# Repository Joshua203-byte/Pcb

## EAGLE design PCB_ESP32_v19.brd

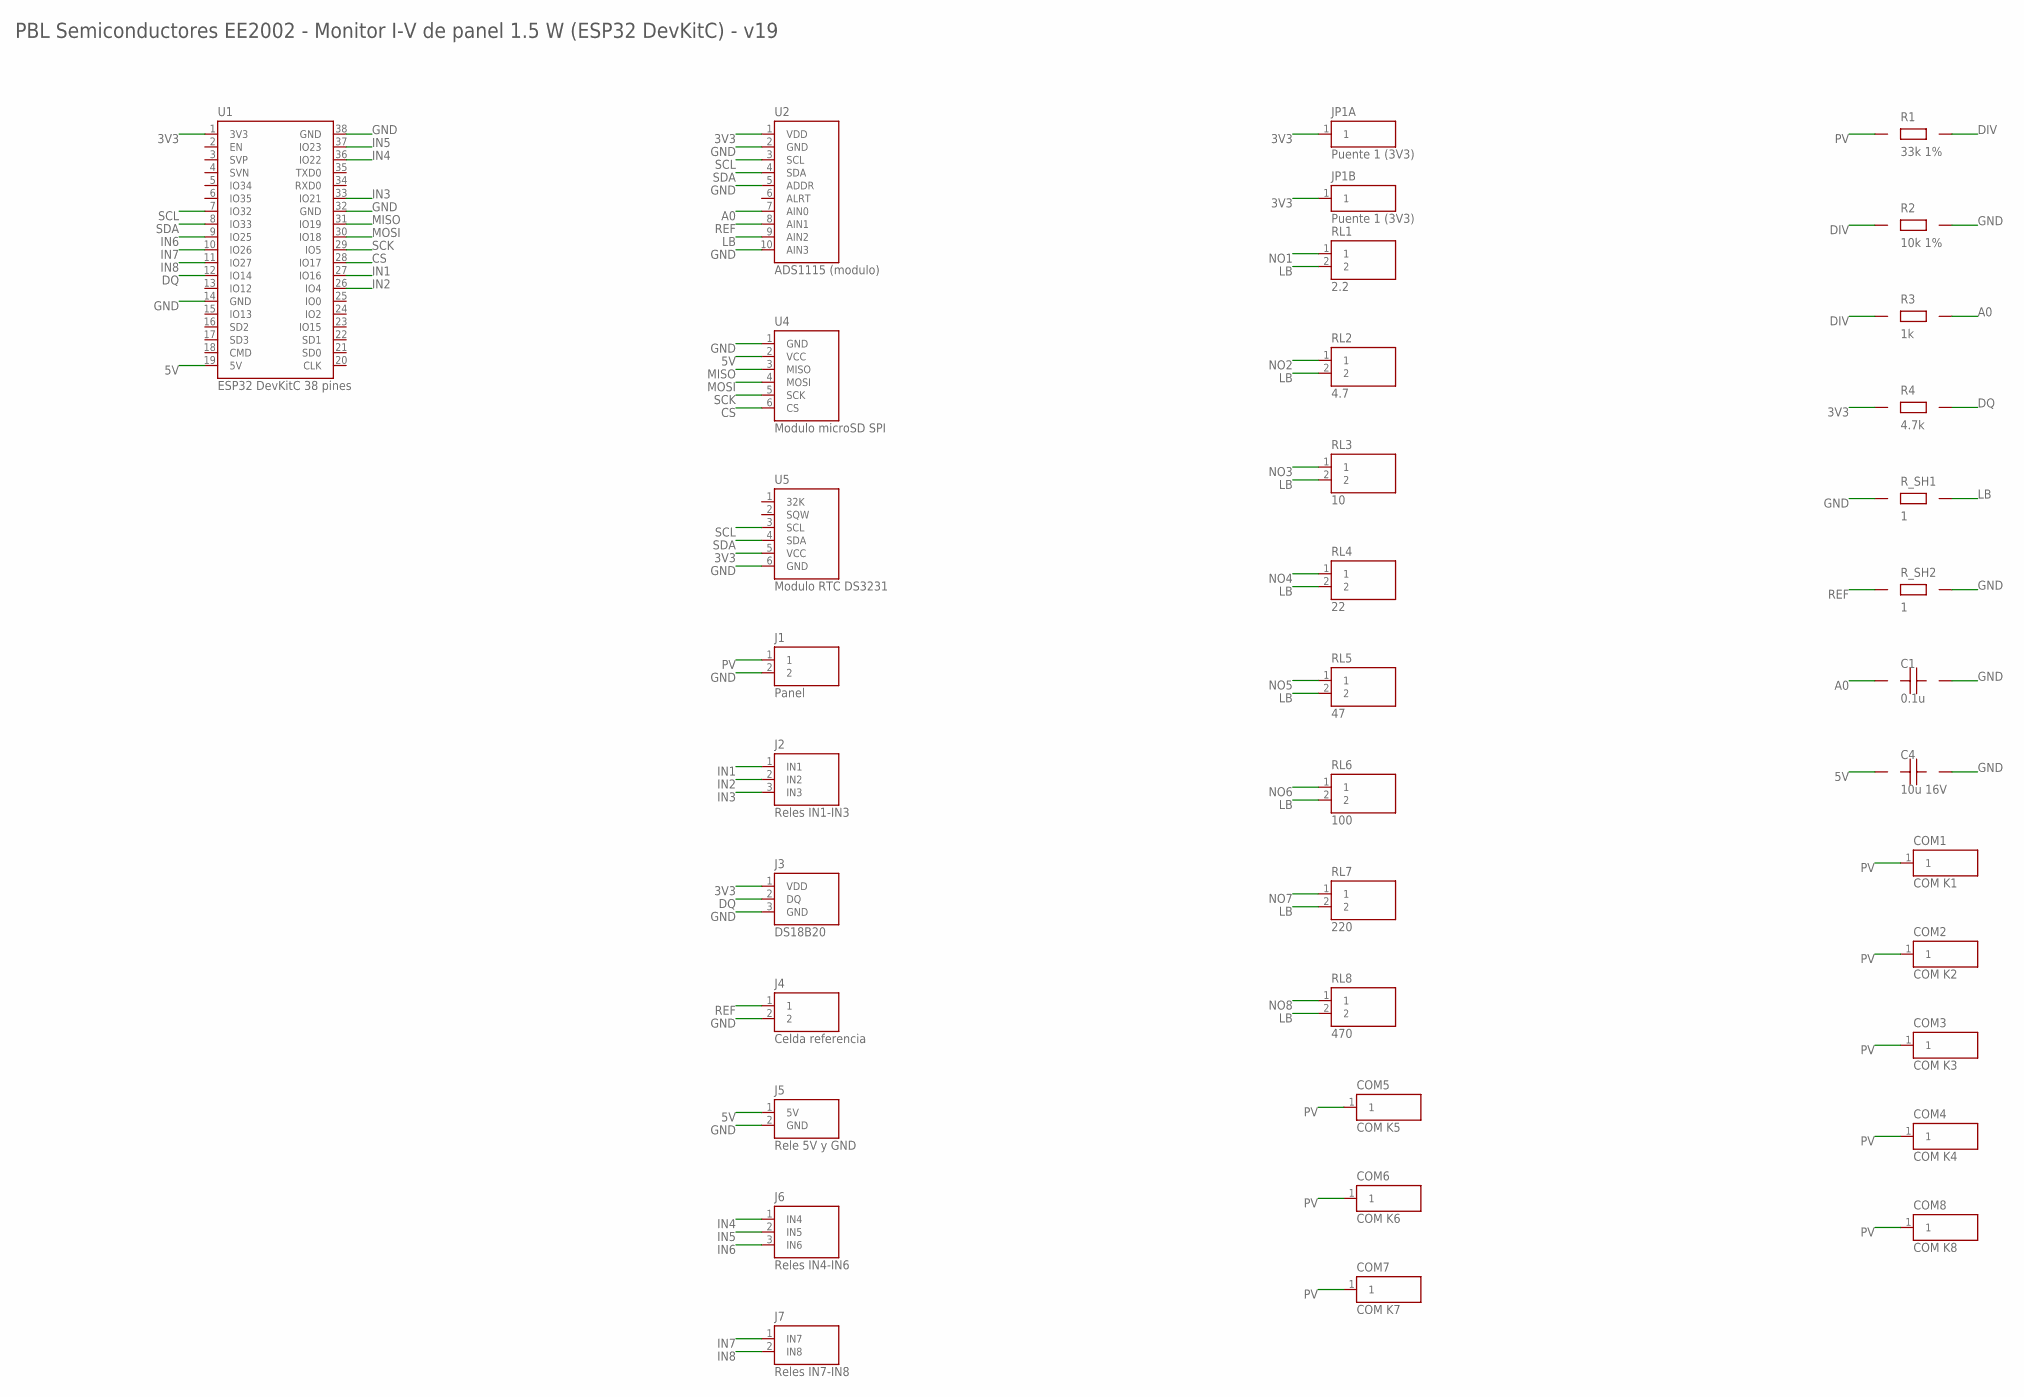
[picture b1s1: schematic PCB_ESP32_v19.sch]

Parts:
C1: 0.1u; CAP_5MM
C4: 10u 16V; CAP_E_2_54
COM1: COM K1; WIREPAD
COM2: COM K2; WIREPAD
COM3: COM K3; WIREPAD
COM4: COM K4; WIREPAD
COM5: COM K5; WIREPAD
COM6: COM K6; WIREPAD
COM7: COM K7; WIREPAD
COM8: COM K8; WIREPAD
J1: Panel; TERM2_5MM
J2: Reles IN1-IN3; MALE_1X03
J3: DS18B20; MALE_1X03
J4: Celda referencia; TERM2_5MM
J5: Rele 5V y GND; MALE_1X02
J6: Reles IN4-IN6; MALE_1X03
J7: Reles IN7-IN8; MALE_1X02
JP1A, JP1B: Puente 1 (3V3); JPAD
R1: 33k 1%; RES_V
R2: 10k 1%; RES_V
R3: 1k; RES_V
R4: 4.7k; RES_V
RL1: 2.2; RES_H_T
RL2: 4.7; RES_H_T
RL3: 10; RES_H_T
RL4: 22; RES_H_T
RL5: 47; RES_H_T
RL6: 100; RES_H_T
RL7: 220; RES_H_T
RL8: 470; RES_H_T
R_SH1, R_SH2: 1; RES_V
U1: ESP32 DevKitC 38 pines; ESP32_DEVKIT38
U2: ADS1115 (modulo); SOCKET_1X10
U4: Modulo microSD SPI; SOCKET_1X06
U5: Modulo RTC DS3231; SOCKET_1X06

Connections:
3V3: J3.1 (VDD), JP1A.1, JP1B.1, R4.1, U1.1 (3V3), U2.1 (VDD), U5.5 (VCC)
5V: C4.1 (+), J5.1 (5V), U1.19 (5V), U4.2 (VCC)
A0: C1.1, R3.2, U2.7 (AIN0)
CS: U1.28 (IO17), U4.6 (CS)
DIV: R1.2, R2.1, R3.1
DQ: J3.2 (DQ), R4.2, U1.12 (IO14)
GND: C1.2, C4.2 (-), J1.2, J3.3 (GND), J4.2, J5.2 (GND), R2.2, R_SH1.1, R_SH2.2, U1.14 (GND), U1.32 (GND), U1.38 (GND), U2.2 (GND), U2.5 (ADDR), U2.10 (AIN3), U4.1 (GND), U5.6 (GND)
IN1: J2.1 (IN1), U1.27 (IO16)
IN2: J2.2 (IN2), U1.26 (IO4)
IN3: J2.3 (IN3), U1.33 (IO21)
IN4: J6.1 (IN4), U1.36 (IO22)
IN5: J6.2 (IN5), U1.37 (IO23)
IN6: J6.3 (IN6), U1.9 (IO25)
IN7: J7.1 (IN7), U1.10 (IO26)
IN8: J7.2 (IN8), U1.11 (IO27)
LB: RL1.2, RL2.2, RL3.2, RL4.2, RL5.2, RL6.2, RL7.2, RL8.2, R_SH1.2, U2.9 (AIN2)
MISO: U1.31 (IO19), U4.3 (MISO)
MOSI: U1.30 (IO18), U4.4 (MOSI)
NO1: RL1.1
NO2: RL2.1
NO3: RL3.1
NO4: RL4.1
NO5: RL5.1
NO6: RL6.1
NO7: RL7.1
NO8: RL8.1
PV: COM1.1, COM2.1, COM3.1, COM4.1, COM5.1, COM6.1, COM7.1, COM8.1, J1.1, R1.1
REF: J4.1, R_SH2.1, U2.8 (AIN1)
SCK: U1.29 (IO5), U4.5 (SCK)
SCL: U1.7 (IO32), U2.3 (SCL), U5.3 (SCL)
SDA: U1.8 (IO33), U2.4 (SDA), U5.4 (SDA)

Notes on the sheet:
PBL Semiconductores EE2002 - Monitor I-V de panel 1.5 W (ESP32 DevKitC) - v19

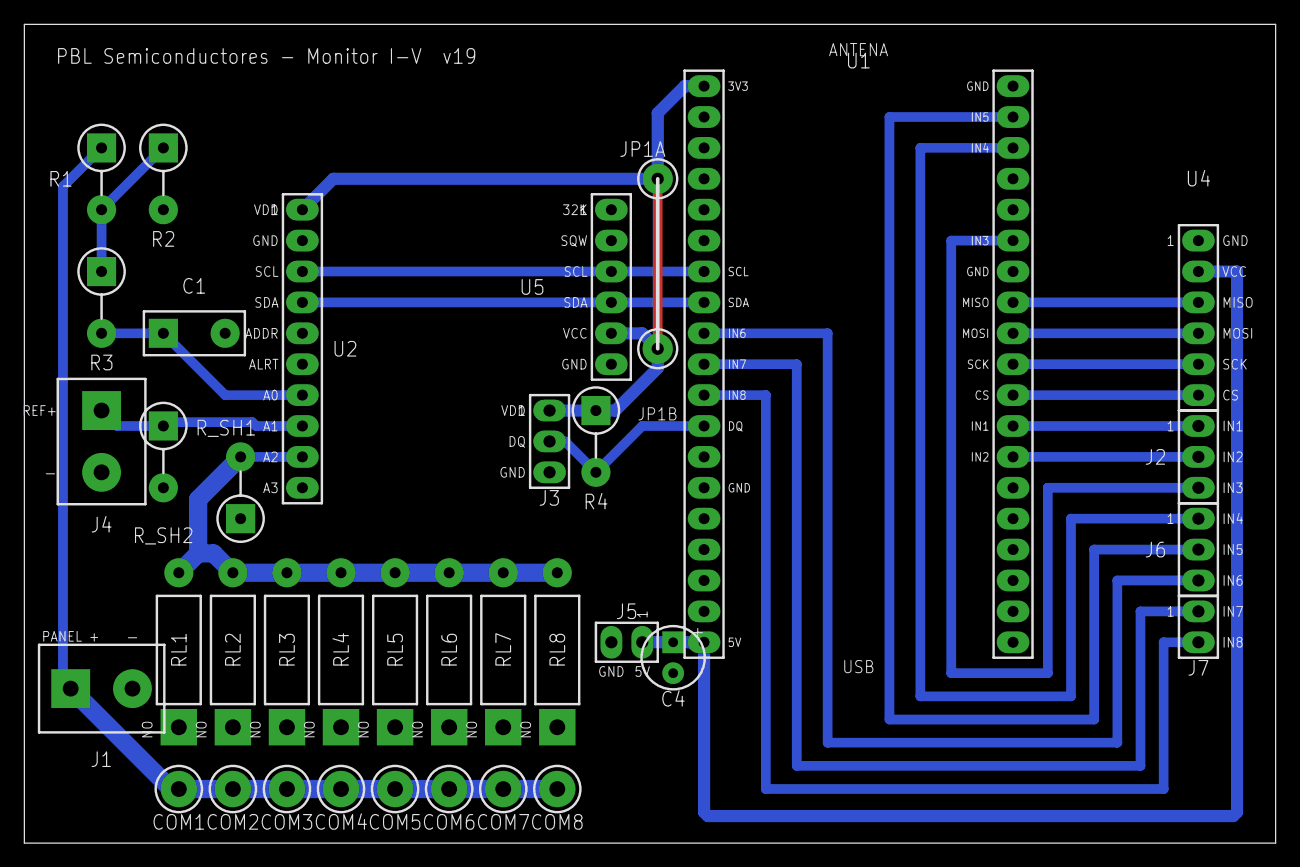
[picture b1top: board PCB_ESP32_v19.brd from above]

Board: 2 copper layers, 102.9 x 67.3 mm, 37 parts (0 on the bottom side), 23 nets.

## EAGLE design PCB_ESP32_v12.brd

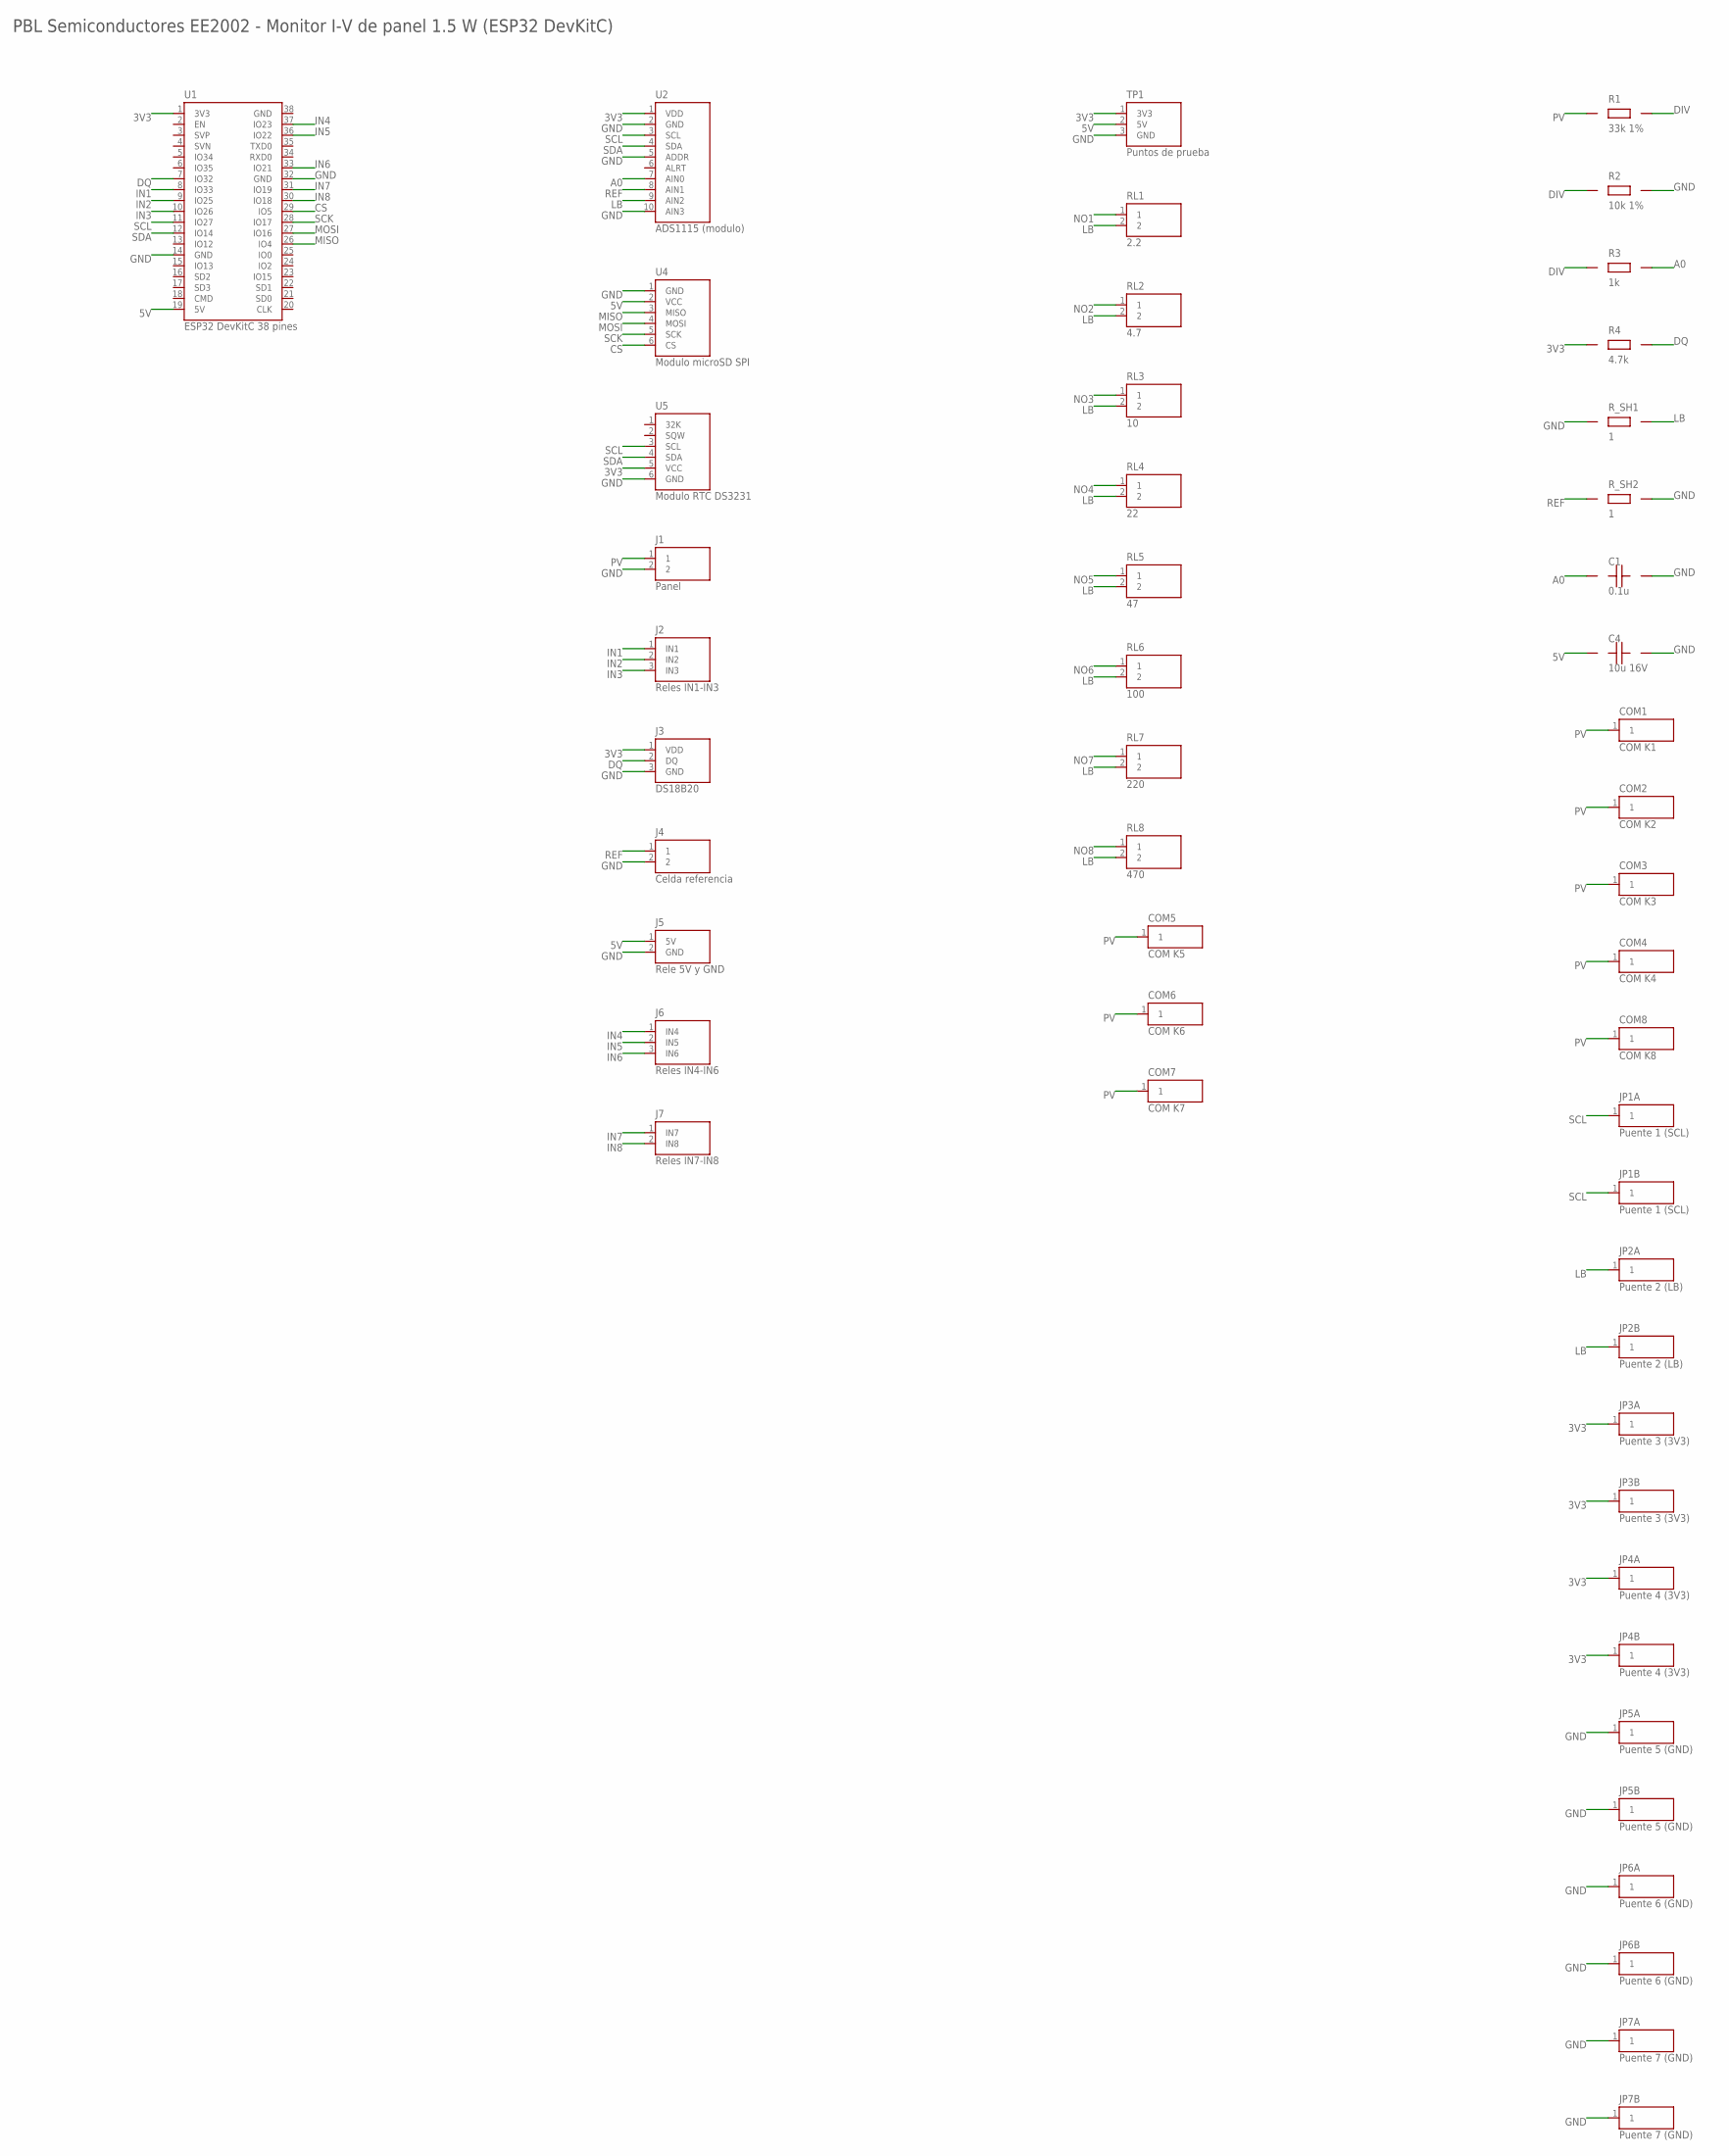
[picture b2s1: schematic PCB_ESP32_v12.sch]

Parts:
C1: 0.1u; CAP_5MM
C4: 10u 16V; CAP_E_2_54
COM1: COM K1; WIREPAD
COM2: COM K2; WIREPAD
COM3: COM K3; WIREPAD
COM4: COM K4; WIREPAD
COM5: COM K5; WIREPAD
COM6: COM K6; WIREPAD
COM7: COM K7; WIREPAD
COM8: COM K8; WIREPAD
J1: Panel; TERM2_5MM
J2: Reles IN1-IN3; MALE_1X03
J3: DS18B20; MALE_1X03
J4: Celda referencia; TERM2_5MM
J5: Rele 5V y GND; MALE_1X02
J6: Reles IN4-IN6; MALE_1X03
J7: Reles IN7-IN8; MALE_1X02
JP1A, JP1B: Puente 1 (SCL); JPAD
JP2A, JP2B: Puente 2 (LB); JPAD
JP3A, JP3B: Puente 3 (3V3); JPAD
JP4A, JP4B: Puente 4 (3V3); JPAD
JP5A, JP5B: Puente 5 (GND); JPAD
JP6A, JP6B: Puente 6 (GND); JPAD
JP7A, JP7B: Puente 7 (GND); JPAD
R1: 33k 1%; RES_V
R2: 10k 1%; RES_V
R3: 1k; RES_V
R4: 4.7k; RES_V
RL1: 2.2; RES_H_T
RL2: 4.7; RES_H_T
RL3: 10; RES_H_T
RL4: 22; RES_H_T
RL5: 47; RES_H_T
RL6: 100; RES_H_T
RL7: 220; RES_H_T
RL8: 470; RES_H_T
R_SH1, R_SH2: 1; RES_V
TP1: Puntos de prueba; MALE_1X03
U1: ESP32 DevKitC 38 pines; ESP32_DEVKIT38
U2: ADS1115 (modulo); SOCKET_1X10
U4: Modulo microSD SPI; SOCKET_1X06
U5: Modulo RTC DS3231; SOCKET_1X06

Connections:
3V3: J3.1 (VDD), JP3A.1, JP3B.1, JP4A.1, JP4B.1, R4.1, TP1.1 (3V3), U1.1 (3V3), U2.1 (VDD), U5.5 (VCC)
5V: C4.1 (+), J5.1 (5V), TP1.2 (5V), U1.19 (5V), U4.2 (VCC)
A0: C1.1, R3.2, U2.7 (AIN0)
CS: U1.29 (IO5), U4.6 (CS)
DIV: R1.2, R2.1, R3.1
DQ: J3.2 (DQ), R4.2, U1.7 (IO32)
GND: C1.2, C4.2 (-), J1.2, J3.3 (GND), J4.2, J5.2 (GND), JP5A.1, JP5B.1, JP6A.1, JP6B.1, JP7A.1, JP7B.1, R2.2, R_SH1.1, R_SH2.2, TP1.3 (GND), U1.14 (GND), U1.32 (GND), U2.2 (GND), U2.5 (ADDR), U2.10 (AIN3), U4.1 (GND), U5.6 (GND)
IN1: J2.1 (IN1), U1.8 (IO33)
IN2: J2.2 (IN2), U1.9 (IO25)
IN3: J2.3 (IN3), U1.10 (IO26)
IN4: J6.1 (IN4), U1.37 (IO23)
IN5: J6.2 (IN5), U1.36 (IO22)
IN6: J6.3 (IN6), U1.33 (IO21)
IN7: J7.1 (IN7), U1.31 (IO19)
IN8: J7.2 (IN8), U1.30 (IO18)
LB: JP2A.1, JP2B.1, RL1.2, RL2.2, RL3.2, RL4.2, RL5.2, RL6.2, RL7.2, RL8.2, R_SH1.2, U2.9 (AIN2)
MISO: U1.26 (IO4), U4.3 (MISO)
MOSI: U1.27 (IO16), U4.4 (MOSI)
NO1: RL1.1
NO2: RL2.1
NO3: RL3.1
NO4: RL4.1
NO5: RL5.1
NO6: RL6.1
NO7: RL7.1
NO8: RL8.1
PV: COM1.1, COM2.1, COM3.1, COM4.1, COM5.1, COM6.1, COM7.1, COM8.1, J1.1, R1.1
REF: J4.1, R_SH2.1, U2.8 (AIN1)
SCK: U1.28 (IO17), U4.5 (SCK)
SCL: JP1A.1, JP1B.1, U1.11 (IO27), U2.3 (SCL), U5.3 (SCL)
SDA: U1.12 (IO14), U2.4 (SDA), U5.4 (SDA)

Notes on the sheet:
PBL Semiconductores EE2002 - Monitor I-V de panel 1.5 W (ESP32 DevKitC)

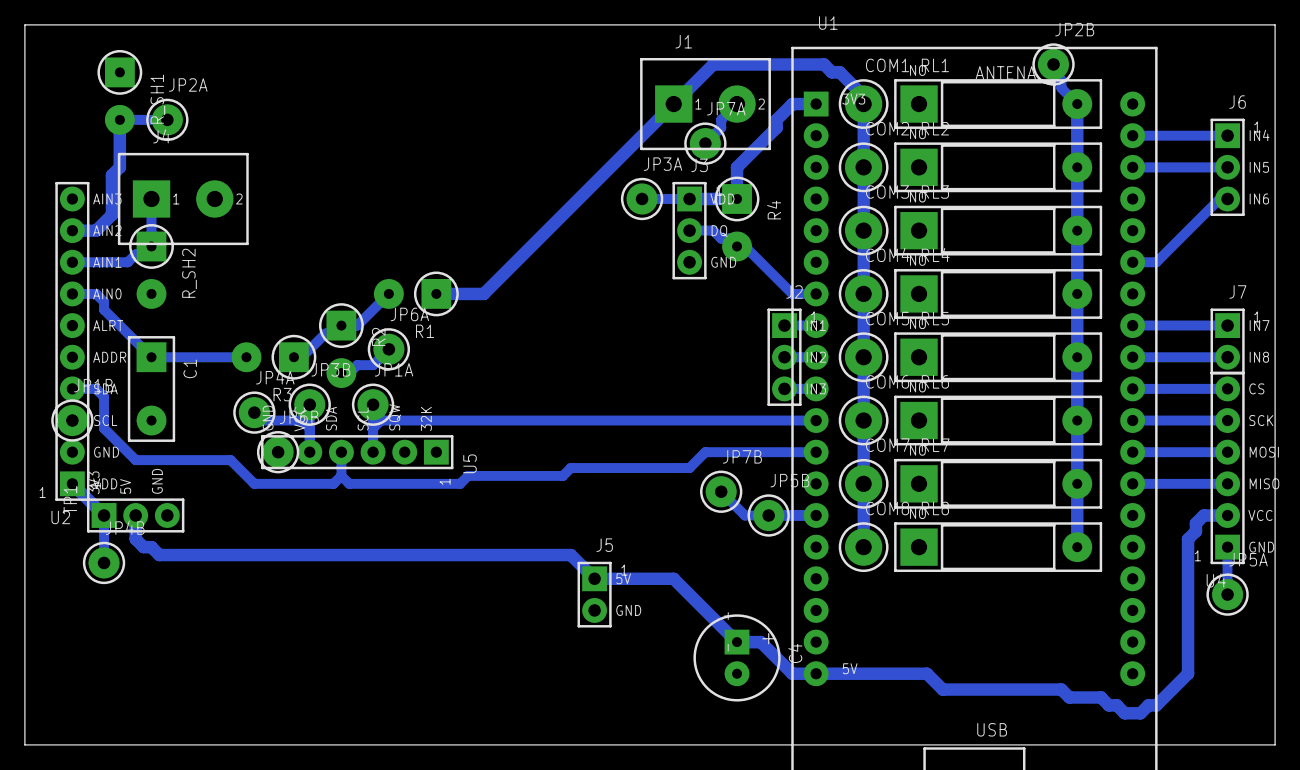
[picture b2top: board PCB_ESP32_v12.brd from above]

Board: 2 copper layers, 100.3 x 57.8 mm, 50 parts (0 on the bottom side), 23 nets.
